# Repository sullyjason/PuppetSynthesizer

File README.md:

# Puppet Synth

A collaborative project between ZHdK's Departments of Interaction Design and Game Design, commissioned by Museum für Gestaltung.

## Project brief

For the Exhibition "Museum of the Future" in 2025, Zürich's Museum für Gestaltung has commissioned ZHdK to develop a series of interactive installations paying tribute to Sophie Täuber Arp's infamous wooden marionettes that she created for the play _King Stag_.

### Team

The team consists of five members coming from various disciplines.

- Lisa Bach [@julielionheart](https://github.com/julielionheart) - Unity 3D and creative direction
- Silvan Roth [@sullyjason](https://github.com/sullyjason) - Interface design and hardware
- Jan Hügli - Prototyping and production
- Jan Thürig [@JanThuering](https://github.com/JanThuering) - Unity 3D and firmware
- Jan Espig [@Jespig](https://github.com/Jespig) - Visual design
- David Bock [@davidoffcw](https://github.com/davidoffcw) & Lars Kristian [@larskristianblom](https://github.com/larskristianblom) - Sound design

## Concept

Puppet Synth is a digital reinterpretation of Sophie Taeuber-Arp’s avant-garde puppetry for King Stag, breaking with traditional visual and performative conventions. Inspired by Rudolf Laban’s choreographic notation and Taeuber-Arp’s expressive dance practice, this project brings the puppets’ gestures into the digital realm. Users are invited to choreograph puppet movements themselves. Visually, Puppet Synth renders these complex motion sequences as wave-like frequency patterns, making them both tangible and analyzable.

## Implementation

```mermaid
flowchart TD
    Interface["🎛️ Physical Interface"] --> Arduino["Analog Signal processing"]
    Arduino --> MIDI["🎹 MIDI / Control Signal"]

    MIDI --> WaveSynthesis["Wave synthesis"] --> FMOD["🔊 FMOD (Audio Synthesis)"]
    WaveSynthesis --> UnityAnim["🕺 Unity Animator (Puppet Control)"]

    FMOD --> Audio["🎵 Dynamic Audio Output"]
    UnityAnim --> Visual["🎭 Puppet Animation in Unity"]

    Audio & Visual --> Output["🎬 Final Experience (Live AV Performance)"]
```
### Interface

The interface consists of 5 types of inputs: rotary switches, smooth rotary potentiometers, linear potentiometers (faders), and momentary 3 position toggle switches.

### Visual Style

The visual style takes inspiration from Sophie Täuber-Arp's minimal color palette and simple revolved shapes that make up the marionettes.

## Experience

## Repository files

- Firmware (arduino code)
- Electronic Design files
- CAD drawings and STLs
- Unity build and project files
- FMOD code

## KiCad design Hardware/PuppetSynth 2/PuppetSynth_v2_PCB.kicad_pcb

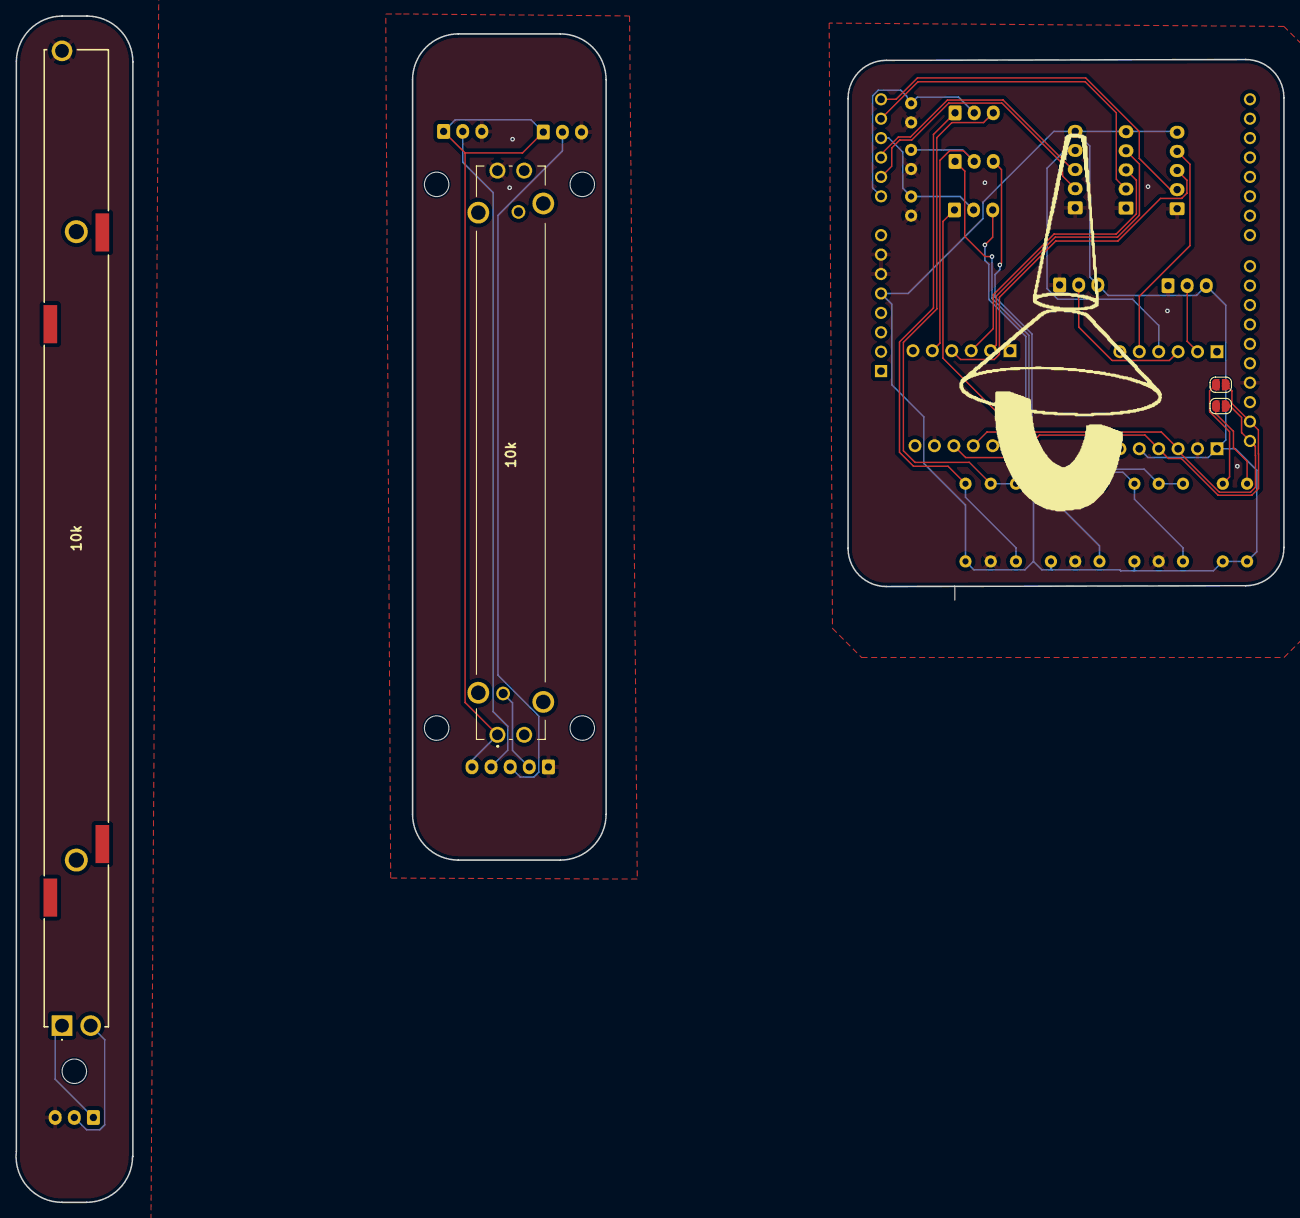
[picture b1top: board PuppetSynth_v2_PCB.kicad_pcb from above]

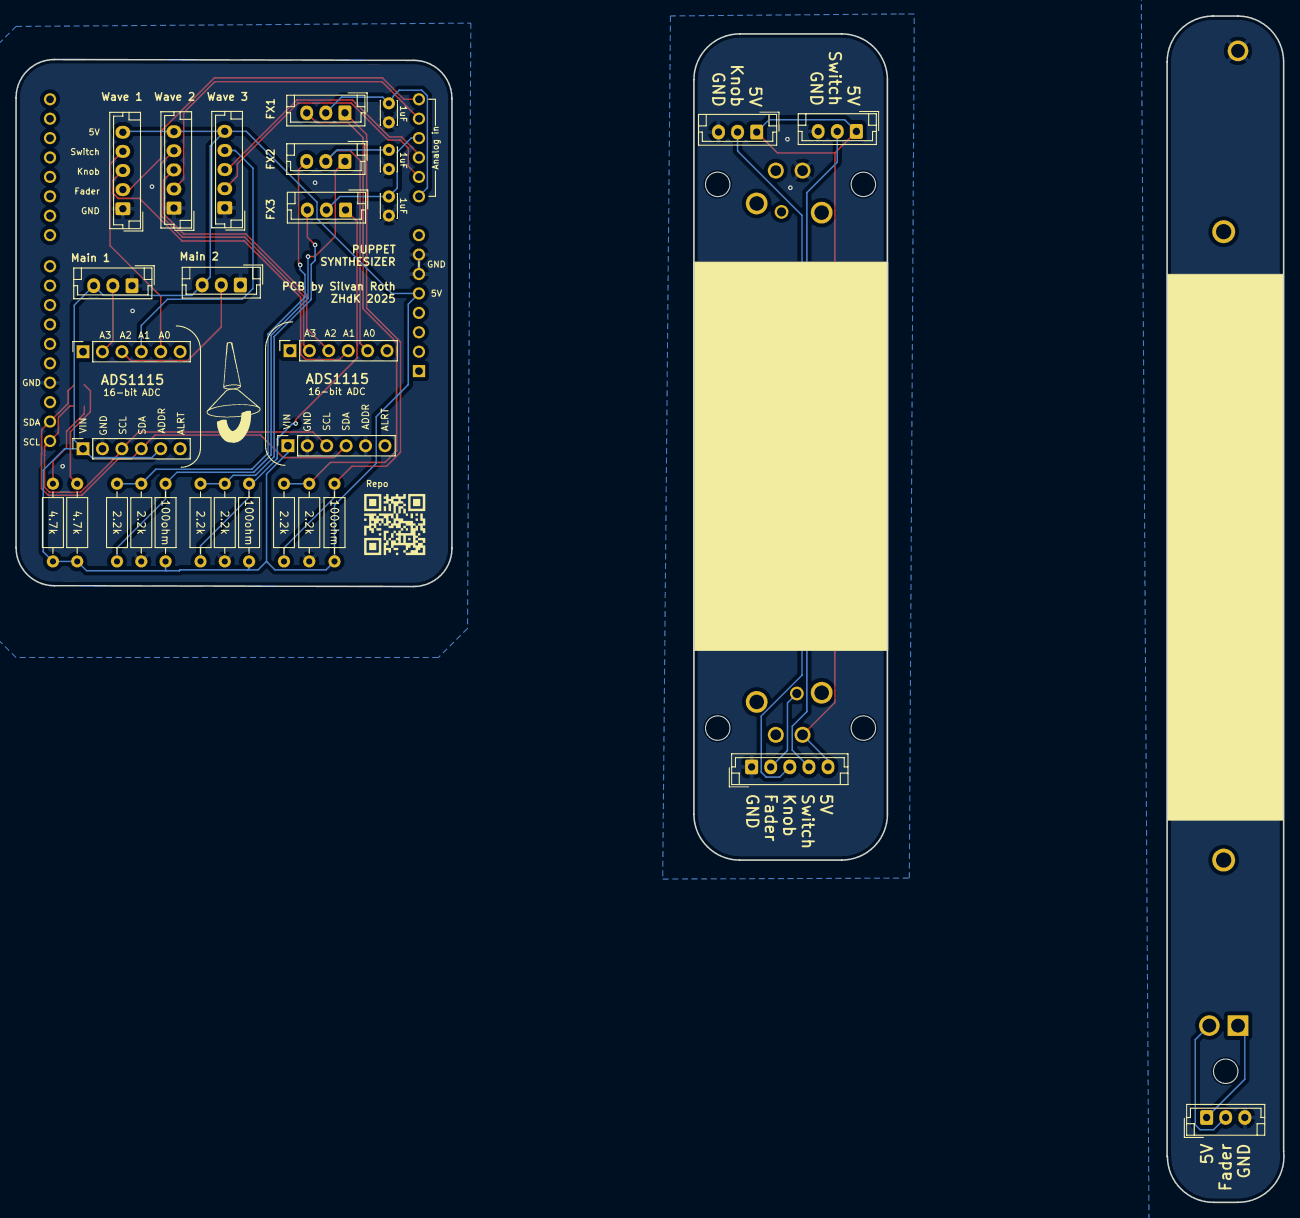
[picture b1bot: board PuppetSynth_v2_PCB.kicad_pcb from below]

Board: 2 copper layers, 57.0 x 68.9 mm, 40 parts (30 on the bottom side), 26 nets.

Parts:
10k: R_Potentiometer; PS6020MC1BR10K
10k#2: R_Potentiometer; PS1001B1BR10K
A1: Arduino_Leonardo; Arduino_UNO_R3
C3, C4, C5: 1uF; C_Disc_D3.0mm_W2.0mm_P2.50mm
H1, H2, H3, H4, H13: MountingHole_M3; MountingHole_3.2mm_M3
J3, J11, J12, J16, J20, J24, J25, J26: JST_03; JST_EH_B3B-EH-A_1x03_P2.50mm_Vertical
J5, J13, J14, J15: JST_05; JST_EH_B5B-EH-A_1x05_P2.50mm_Vertical
J8, J9, J10, J19: PINHD_1x6_Female; PinSocket_1x06_P2.54mm_Vertical
JP1, JP2: Jumper_2_Bridged; SolderJumper-2_P1.3mm_Open_RoundedPad1.0x1.5mm
R1, R2: 4.7k; R_Axial_DIN0207_L6.3mm_D2.5mm_P10.16mm_Horizontal
R4, R5, R10, R11, R13, R14: 2.2k; R_Axial_DIN0207_L6.3mm_D2.5mm_P10.16mm_Horizontal
R9, R12, R17: 100ohm; R_Axial_DIN0207_L6.3mm_D2.5mm_P10.16mm_Horizontal

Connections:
+5V: 10k.1, 10k#2.1, A1.5 (+5V), J3.1, J5.5, J8.1, J10.1, J10.5, J11.3, J12.3, J13.5, J14.5, J15.5, J16.1, J20.1, R1.2, R2.2, R9.2, R12.2, R17.2
GND: 10k.3, 10k#2.3, A1.6 (GND), A1.7 (GND), A1.29 (GND), C3.2, C4.2, C5.2, J3.3, J5.1, J8.2, J8.5, J10.2, J11.1, J12.1, J13.1, J14.1, J15.1, J16.3, J20.3, R5.1, R10.1, R13.1
Knob_1: J5.3, J9.4, J13.3, J20.2
Knob_2: J9.3, J14.3
Knob_3: A1.11 (A2), J15.3
Main_1: 10k#2.2, J3.2, J11.2, J19.2
Main_2: J12.2, J19.3
unnamed: C3.1, J24.2
unnamed: J24.1, R4.2, R9.1
unnamed: J24.3, R4.1, R5.2
unnamed: J25.1, R11.2, R12.1
unnamed: J25.3, R10.2, R11.1
unnamed: J26.1, R14.2, R17.1
unnamed: J26.3, R13.2, R14.1
unnamed: JP1.1 (A), R1.1
unnamed: JP2.1 (A), R2.1
SCL: A1.32 (SCL/D3), J8.3, J10.3, JP1.2 (B)
SDA: A1.31 (SDA/D2), J8.4, J10.4, JP2.2 (B)
Small_Fader_1: 10k.2, A1.14 (A5), J5.2, J13.2
Small_Fader_2: A1.13 (A4), J14.2
Small_Fader_3: A1.10 (A1), J15.2
Switch_1: J5.4, J13.4, J16.2, J19.5
Switch_2: J9.2, J14.4
Switch_3: J15.4, J19.4
Toggle_2: C4.1, J9.5, J25.2
Toggle_3: A1.12 (A3), C5.1, J26.2

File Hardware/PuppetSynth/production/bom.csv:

Designator,Footprint,Quantity,Value,LCSC Part #
10K_2,PS6020MC1BR10K,1,R_Potentiometer,
10K,PS1001B1BR10K,1,R_Potentiometer,
A1,Arduino_UNO_R3,1,Arduino_Leonardo,
"C3, C4, C5",C_Disc_D3.0mm_W2.0mm_P2.50mm,3,1uF,
"H1, H13, H2, H3, H4",MountingHole_3.2mm_M3,5,MountingHole_M3,
"J10, J19, J8, J9",PinSocket_1x06_P2.54mm_Vertical,4,PINHD_1x6_Female,
"J11, J12, J16, J20, J24, J25, J26, J3",JST_EH_B3B-EH-A_1x03_P2.50mm_Vertical,8,JST_03,
"J13, J14, J15, J5",JST_EH_B5B-EH-A_1x05_P2.50mm_Vertical,4,JST_05,
"JP1, JP2",SolderJumper-2_P1.3mm_Open_RoundedPad1.0x1.5mm,2,Jumper_2_Bridged,
"R1, R2",R_Axial_DIN0207_L6.3mm_D2.5mm_P10.16mm_Horizontal,2,4.7k,
"R10, R11, R13, R14, R4, R5",R_Axial_DIN0207_L6.3mm_D2.5mm_P10.16mm_Horizontal,6,2.2k,
"R12, R17, R9",R_Axial_DIN0207_L6.3mm_D2.5mm_P10.16mm_Horizontal,3,100ohm,

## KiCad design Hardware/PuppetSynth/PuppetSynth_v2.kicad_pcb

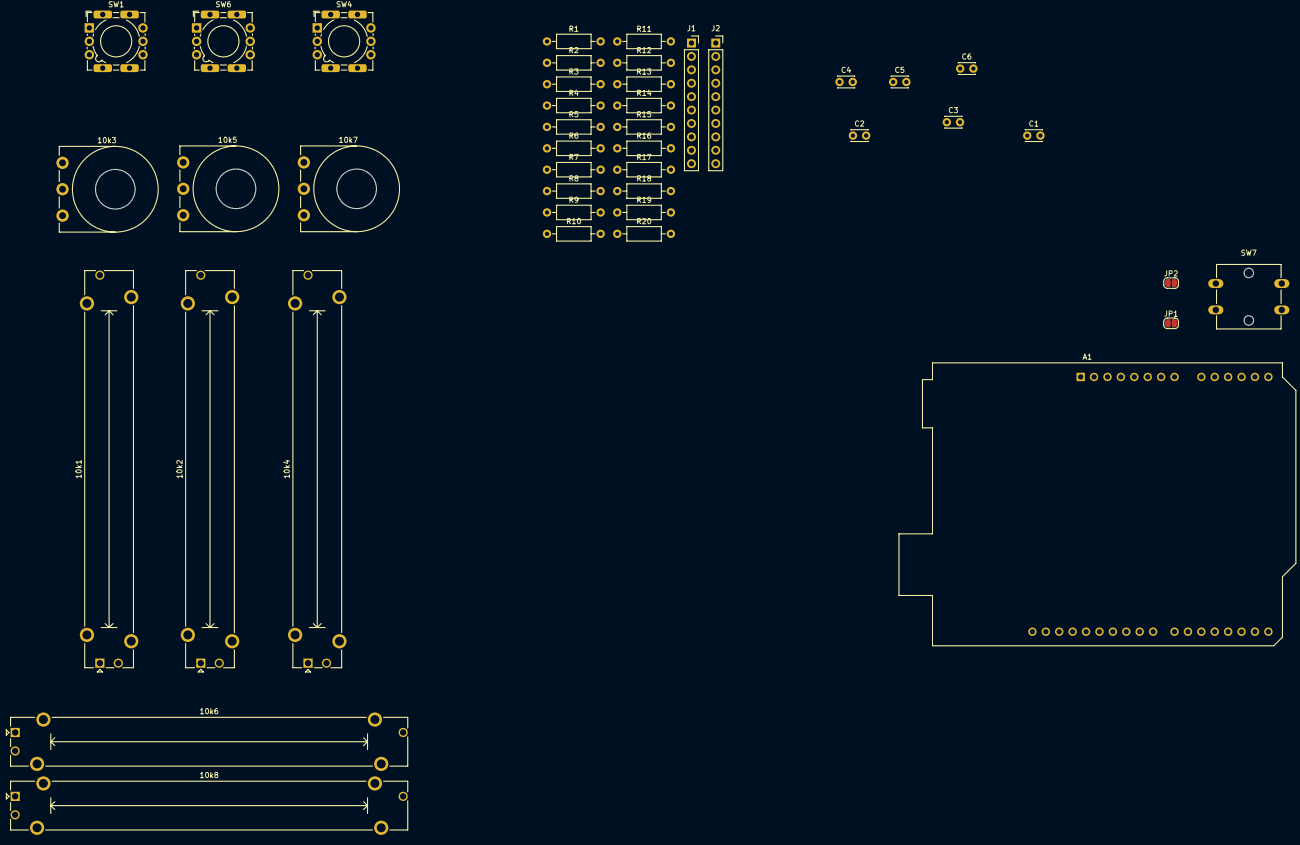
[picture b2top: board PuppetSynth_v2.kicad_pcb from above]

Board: 2 copper layers, 43 parts (0 on the bottom side), 33 nets, no tracks yet.

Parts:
10k1, 10k2, 10k4, 10k6, 10k8: R_Potentiometer; Potentiometer_Bourns_PTA6043_Single_Slide
10k3, 10k5, 10k7: R_Potentiometer; Potentiometer_Piher_T-16L_Single_Vertical_Hole
A1: Arduino_Leonardo; Arduino_UNO_R3
C1, C2, C3, C4, C5, C6: 1uF; C_Disc_D3.0mm_W2.0mm_P2.50mm
J1, J2: ADS1115; PinSocket_1x10_P2.54mm_Vertical
JP1, JP2: Jumper_2_Bridged; SolderJumper-2_P1.3mm_Open_RoundedPad1.0x1.5mm
R1, R2: 4.7k; R_Axial_DIN0207_L6.3mm_D2.5mm_P10.16mm_Horizontal
R3, R6, R18: 100ohm; R_Axial_DIN0207_L6.3mm_D2.5mm_P10.16mm_Horizontal
R4, R5, R7, R8, R9, R10, R11, R12, R13, R14, R15, R16, R17, R19, R20: 2.2k; R_Axial_DIN0207_L6.3mm_D2.5mm_P10.16mm_Horizontal
SW1, SW4, SW6: SW_SP3T_NR01103; SW_NKK_NR01
SW7: Switch; SW_SPST_Omron_B3F-40xx

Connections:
1: 10k1.2, A1.9 (A0)
2: 10k2.2, A1.10 (A1)
3: C3.1, J1.7
4: C4.1, J1.8
5: C5.1, J1.9
6: 10k3.2, J1.10
7: 10k5.2, J2.7
8: 10k7.2, J2.8
9: 10k4.2, J2.9
10: 10k6.2, J2.10
11: 10k8.2, A1.11 (A2)
12: A1.12 (A3), R3.1
13: A1.13 (A4), R6.1
14: A1.14 (A5), R18.1
ADDR_1: 10k1.3, 10k2.3, 10k3.3, 10k4.3, 10k5.3, 10k6.3, 10k7.3, 10k8.3, A1.6 (GND), A1.7 (GND), A1.29 (GND), C1.2, C2.2, C3.2, C4.2, C5.2, C6.2, J1.2, J1.5, J2.2, R8.1, R9.2, R12.2, R16.1, R17.2, R20.1, SW1.3, SW4.3, SW6.3, SW7.2
ADDR_2: 10k1.1, 10k2.1, 10k3.1, 10k4.1, 10k5.1, 10k6.1, 10k7.1, 10k8.1, A1.5 (+5V), J1.1, J2.1, J2.5, R1.2, R2.2, R4.2, R7.2, R10.2, R13.2, R15.2, R19.2, SW1.1, SW4.1, SW6.1
unnamed: A1.3 (~RESET), SW7.1
unnamed: JP1.1 (A), R1.1
unnamed: JP2.1 (A), R2.1
unnamed: R4.1, R5.2
unnamed: R5.1, R9.1
unnamed: R7.1, R8.2, SW1.2
unnamed: R10.1, R11.2
unnamed: R11.1, R12.1
unnamed: R13.1, R14.2
unnamed: R14.1, R17.1
unnamed: R15.1, R16.2, SW4.2
unnamed: R19.1, R20.2, SW6.2
unnamed: C2.1, R6.2, SW1.C (Common)
unnamed: C1.1, R3.2, SW4.C (Common)
unnamed: C6.1, R18.2, SW6.C (Common)
SCL: A1.32 (SCL/D3), J1.3, J2.3, JP1.2 (B)
SDA: A1.31 (SDA/D2), J1.4, J2.4, JP2.2 (B)

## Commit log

2025-03-06 Initial push
2025-03-06 Added arduino libraries
2025-03-06 updated and exported schematic
2025-03-09 edit firmware
2025-05-09 Updated code for prototype v2 and updated schematic
2025-05-11 Updated PCBs, Archived 3D models, deleted old schematic
2025-05-11 Added component files
2025-05-15 updated pcb
2025-05-16 organized folders, added missing files
2025-05-18 updated PCB: Rounded traces and shield edges
2025-05-22 Added panel designs, updated readme images
2025-05-23 added unity build
2025-05-30 Updated schematic and PCB
    fixed symbols in schematic, rearranged some parts on PCB, ran traces, aesthetic improvements, fixed layers
2025-08-16 Updates pre exhbition
2025-08-17 minor fixes
2025-08-19 PCB fixes
